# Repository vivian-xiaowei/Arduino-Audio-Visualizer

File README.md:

# Arduino Audio Visualizer

\
*A Grade 12 Computer Engineering Project*

## Overview

The Arduino Audio Visualizing Shield is a music visualizer designed to process audio signals and display them on two 8x8 LED matrix.&#x20;

## Features

- **Audio Input**: Processes audio signals via a 3.5mm headphone jack.
- **LED Visualization**: Displays music in various visual modes on an 8x8 LED matrix.
- **Custom PCB Design**: Designed using KiCad for efficient and compact circuit integration.

## Components Used

- **Arduino Mega 2560**: Microcontroller for processing audio signals and controlling the LED matrix.
- **PCB Board**: Custom-designed circuit board for audio input and LED control.
- **8x8 LED Matrix**: For dynamic visualization of audio signals.
- **3.5mm Audio Connector**: Allows audio input from external devices.

## PCB Design

## Demo Video

Watch the demo video here:

https://github.com/user-attachments/assets/e05b6399-b1d1-4a76-b32d-23b891c7161e

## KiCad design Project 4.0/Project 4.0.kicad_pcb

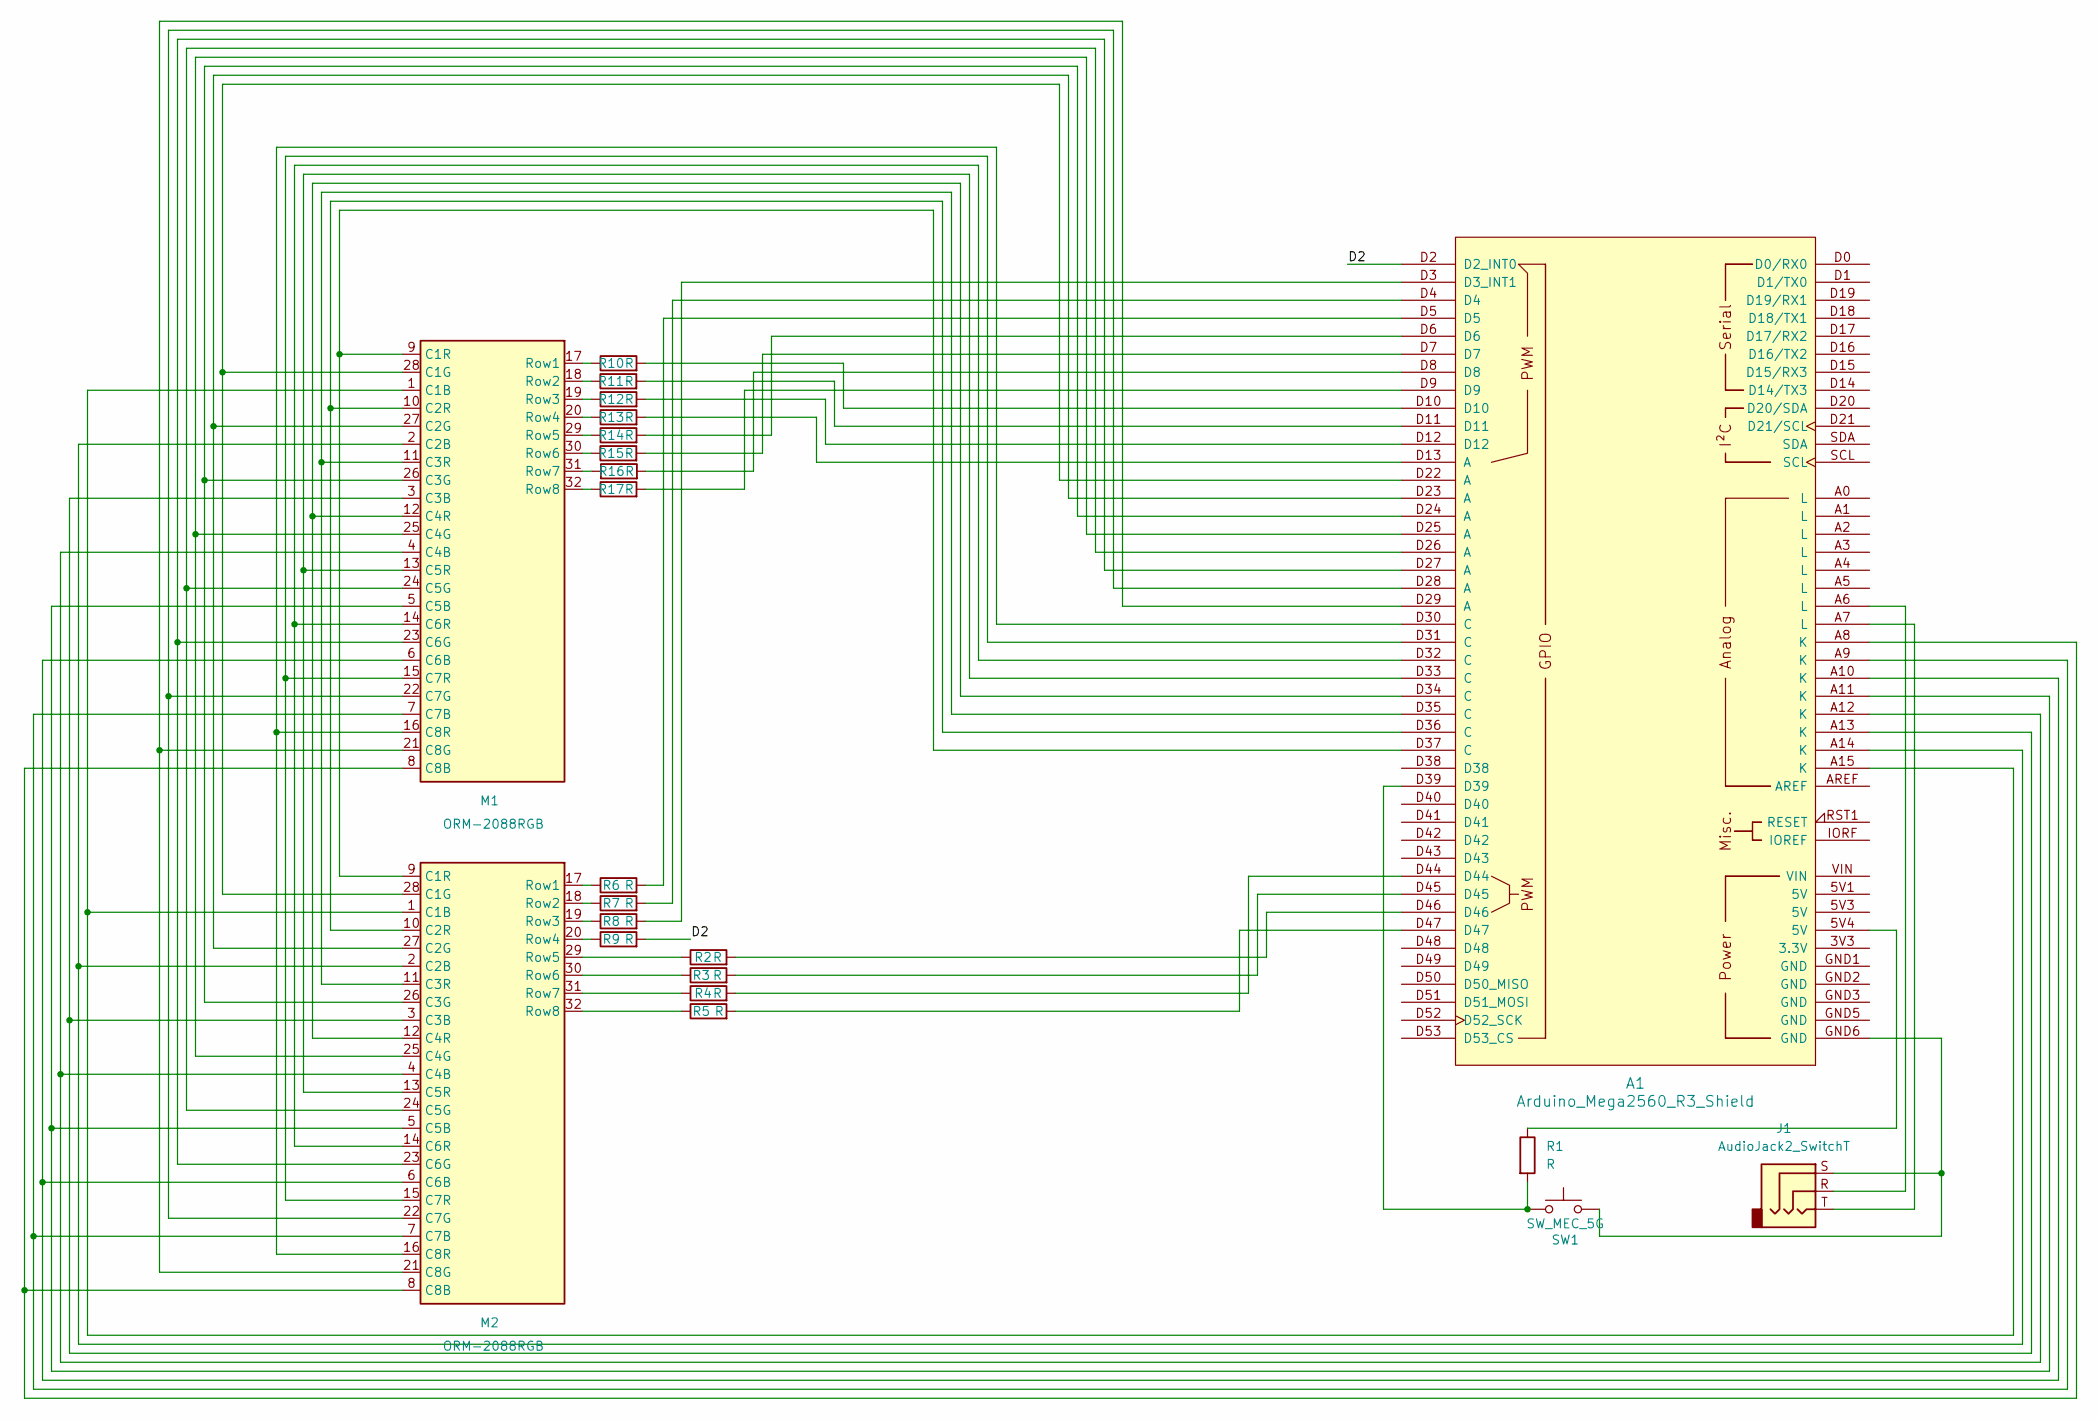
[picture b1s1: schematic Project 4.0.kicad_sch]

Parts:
A1: Arduino_Mega2560_R3_Shield
J1: AudioJack2_SwitchT; 3.5mm Stereo Jack
M1, M2: ORM-2088RGB; led matrix rgb
R1, R2, R3, R4, R5, R6, R7, R8, R9, R10, R11, R12, R13, R14, R15, R16, R17: R; R_Axial_DIN0204_L3.6mm_D1.6mm_P7.62mm_Horizontal
SW1: SW_MEC_5G; SW_1825910-6-4

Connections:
/D2: A1.D2 (D2_INT0), R9.2
unnamed: A1.5V4 (5V), R1.1
unnamed: A1.D13 (A), R13.2
unnamed: A1.D3 (D3_INT1), R8.2
unnamed: A1.GND6 (GND), J1.S, SW1.3 (B), SW1.4 (B)
unnamed: A1.A6 (L), J1.R
unnamed: A1.A7 (L), J1.T
unnamed: A1.D4, R7.2
unnamed: A1.D5, R6.2
unnamed: A1.D6, R14.2
unnamed: A1.D7, R15.2
unnamed: A1.D8, R16.2
unnamed: A1.D9, R17.2
unnamed: A1.D10, R10.2
unnamed: A1.D11, R11.2
unnamed: A1.D12, R12.2
unnamed: A1.D39, R1.2, SW1.1 (A), SW1.2 (A)
unnamed: A1.D44, R4.2
unnamed: A1.D45, R3.2
unnamed: A1.D46, R2.2
unnamed: A1.D47, R5.2
unnamed: A1.A15 (K), M1.1 (C1B), M2.1 (C1B)
unnamed: A1.D22 (A), M1.28 (C1G), M2.28 (C1G)
unnamed: A1.D37 (C), M1.9 (C1R), M2.9 (C1R)
unnamed: A1.A14 (K), M1.2 (C2B), M2.2 (C2B)
unnamed: A1.D23 (A), M1.27 (C2G), M2.27 (C2G)
unnamed: A1.D36 (C), M1.10 (C2R), M2.10 (C2R)
unnamed: A1.A13 (K), M1.3 (C3B), M2.3 (C3B)
unnamed: A1.D24 (A), M1.26 (C3G), M2.26 (C3G)
unnamed: A1.D35 (C), M1.11 (C3R), M2.11 (C3R)
unnamed: A1.A12 (K), M1.4 (C4B), M2.4 (C4B)
unnamed: A1.D25 (A), M1.25 (C4G), M2.25 (C4G)
unnamed: A1.D34 (C), M1.12 (C4R), M2.12 (C4R)
unnamed: A1.A11 (K), M1.5 (C5B), M2.5 (C5B)
unnamed: A1.D26 (A), M1.24 (C5G), M2.24 (C5G)
unnamed: A1.D33 (C), M1.13 (C5R), M2.13 (C5R)
unnamed: A1.A10 (K), M1.6 (C6B), M2.6 (C6B)
unnamed: A1.D27 (A), M1.23 (C6G), M2.23 (C6G)
unnamed: A1.D32 (C), M1.14 (C6R), M2.14 (C6R)
unnamed: A1.A9 (K), M1.7 (C7B), M2.7 (C7B)
unnamed: A1.D28 (A), M1.22 (C7G), M2.22 (C7G)
unnamed: A1.D31 (C), M1.15 (C7R), M2.15 (C7R)
unnamed: A1.A8 (K), M1.8 (C8B), M2.8 (C8B)
unnamed: A1.D29 (A), M1.21 (C8G), M2.21 (C8G)
unnamed: A1.D30 (C), M1.16 (C8R), M2.16 (C8R)
unnamed: M1.17 (Row1), R10.1
unnamed: M1.18 (Row2), R11.1
unnamed: M1.19 (Row3), R12.1
unnamed: M1.20 (Row4), R13.1
unnamed: M1.29 (Row5), R14.1
unnamed: M1.30 (Row6), R15.1
unnamed: M1.31 (Row7), R16.1
unnamed: M1.32 (Row8), R17.1
unnamed: M2.17 (Row1), R6.1
unnamed: M2.18 (Row2), R7.1
unnamed: M2.19 (Row3), R8.1
unnamed: M2.20 (Row4), R9.1
unnamed: M2.29 (Row5), R2.1
unnamed: M2.30 (Row6), R3.1
unnamed: M2.31 (Row7), R4.1
unnamed: M2.32 (Row8), R5.1

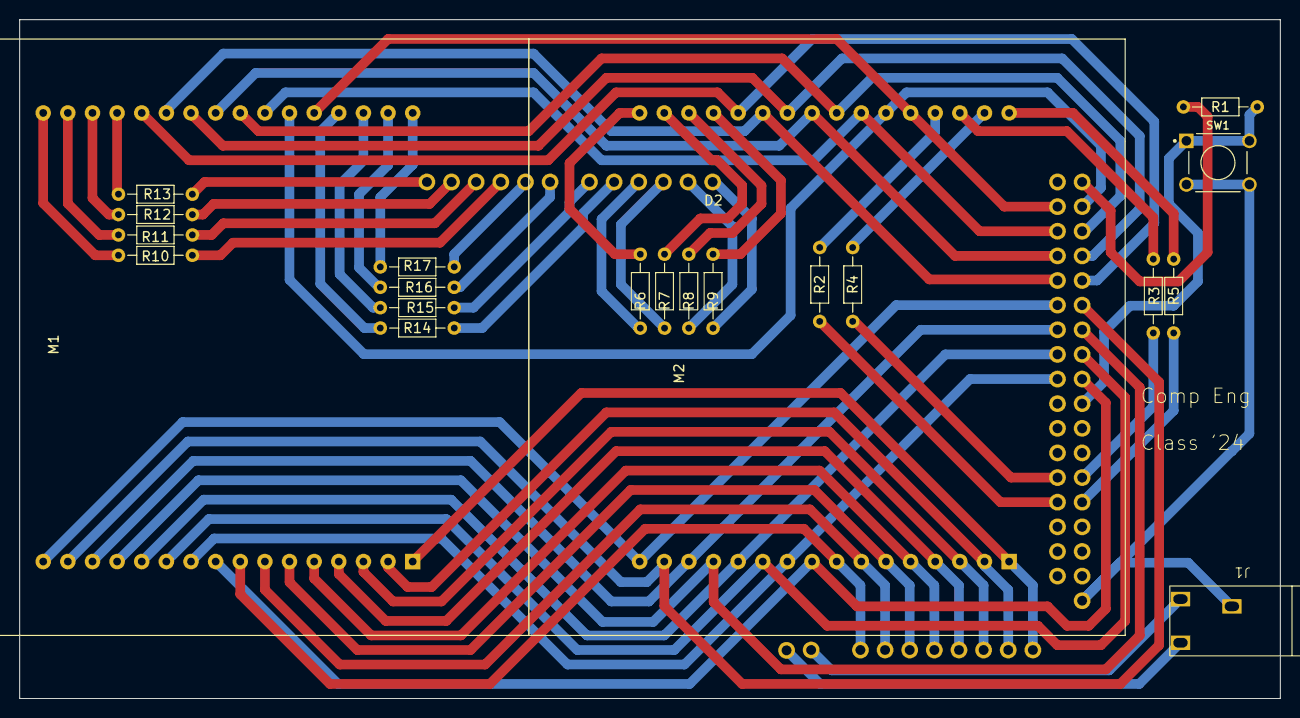
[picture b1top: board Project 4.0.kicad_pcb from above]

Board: 2 copper layers, 130.0 x 70.0 mm, 22 parts (0 on the bottom side), 61 nets.

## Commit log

2024-07-28 Rename Screenshot 2024-07-28 at 10.08.58 AM.png to PCB layout
2024-07-28 Rename Screenshot 2024-07-28 at 10.09.39 AM.png to PCD schematic
2024-12-30 Rename PCB layout to PCB layout.png
2024-12-30 Rename PCD schematic to PCD schematic.png
2024-12-30 Rename to PCB schematic.png
